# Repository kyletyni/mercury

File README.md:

This is a custom PCB and software design I created to compete in the APEC Micromouse 
competition in 2024. The design is based on the ESP32-S3 which is a dual core 
microprocessor. The pcb design was done in Kicad 7.0 and the MCU was programmed using 
the esp-idf utilizing RTOS for time dsensitive task scheduling.

Here is a link to an earlier hardware design running in a maze setting with 
control software:
<a href="https://www.youtube.com/watch?v=heloENtCQyA" target="_blank">Demo Video Link</a>

The PCB schematic consists of IR emitters and receivers, power modules, the MCU, 
gyro, encoders, and buttons.

This is what the PCB looked like when it was delivered.

Assembly complete! Software is still a work in progress, but all modules on the board
function individually as expected.

<div style="display:flex; justify-content:space-between;">

</div>

Layout of front and back layers of the board.
<div style="display:flex; justify-content:space-between;">

</div>

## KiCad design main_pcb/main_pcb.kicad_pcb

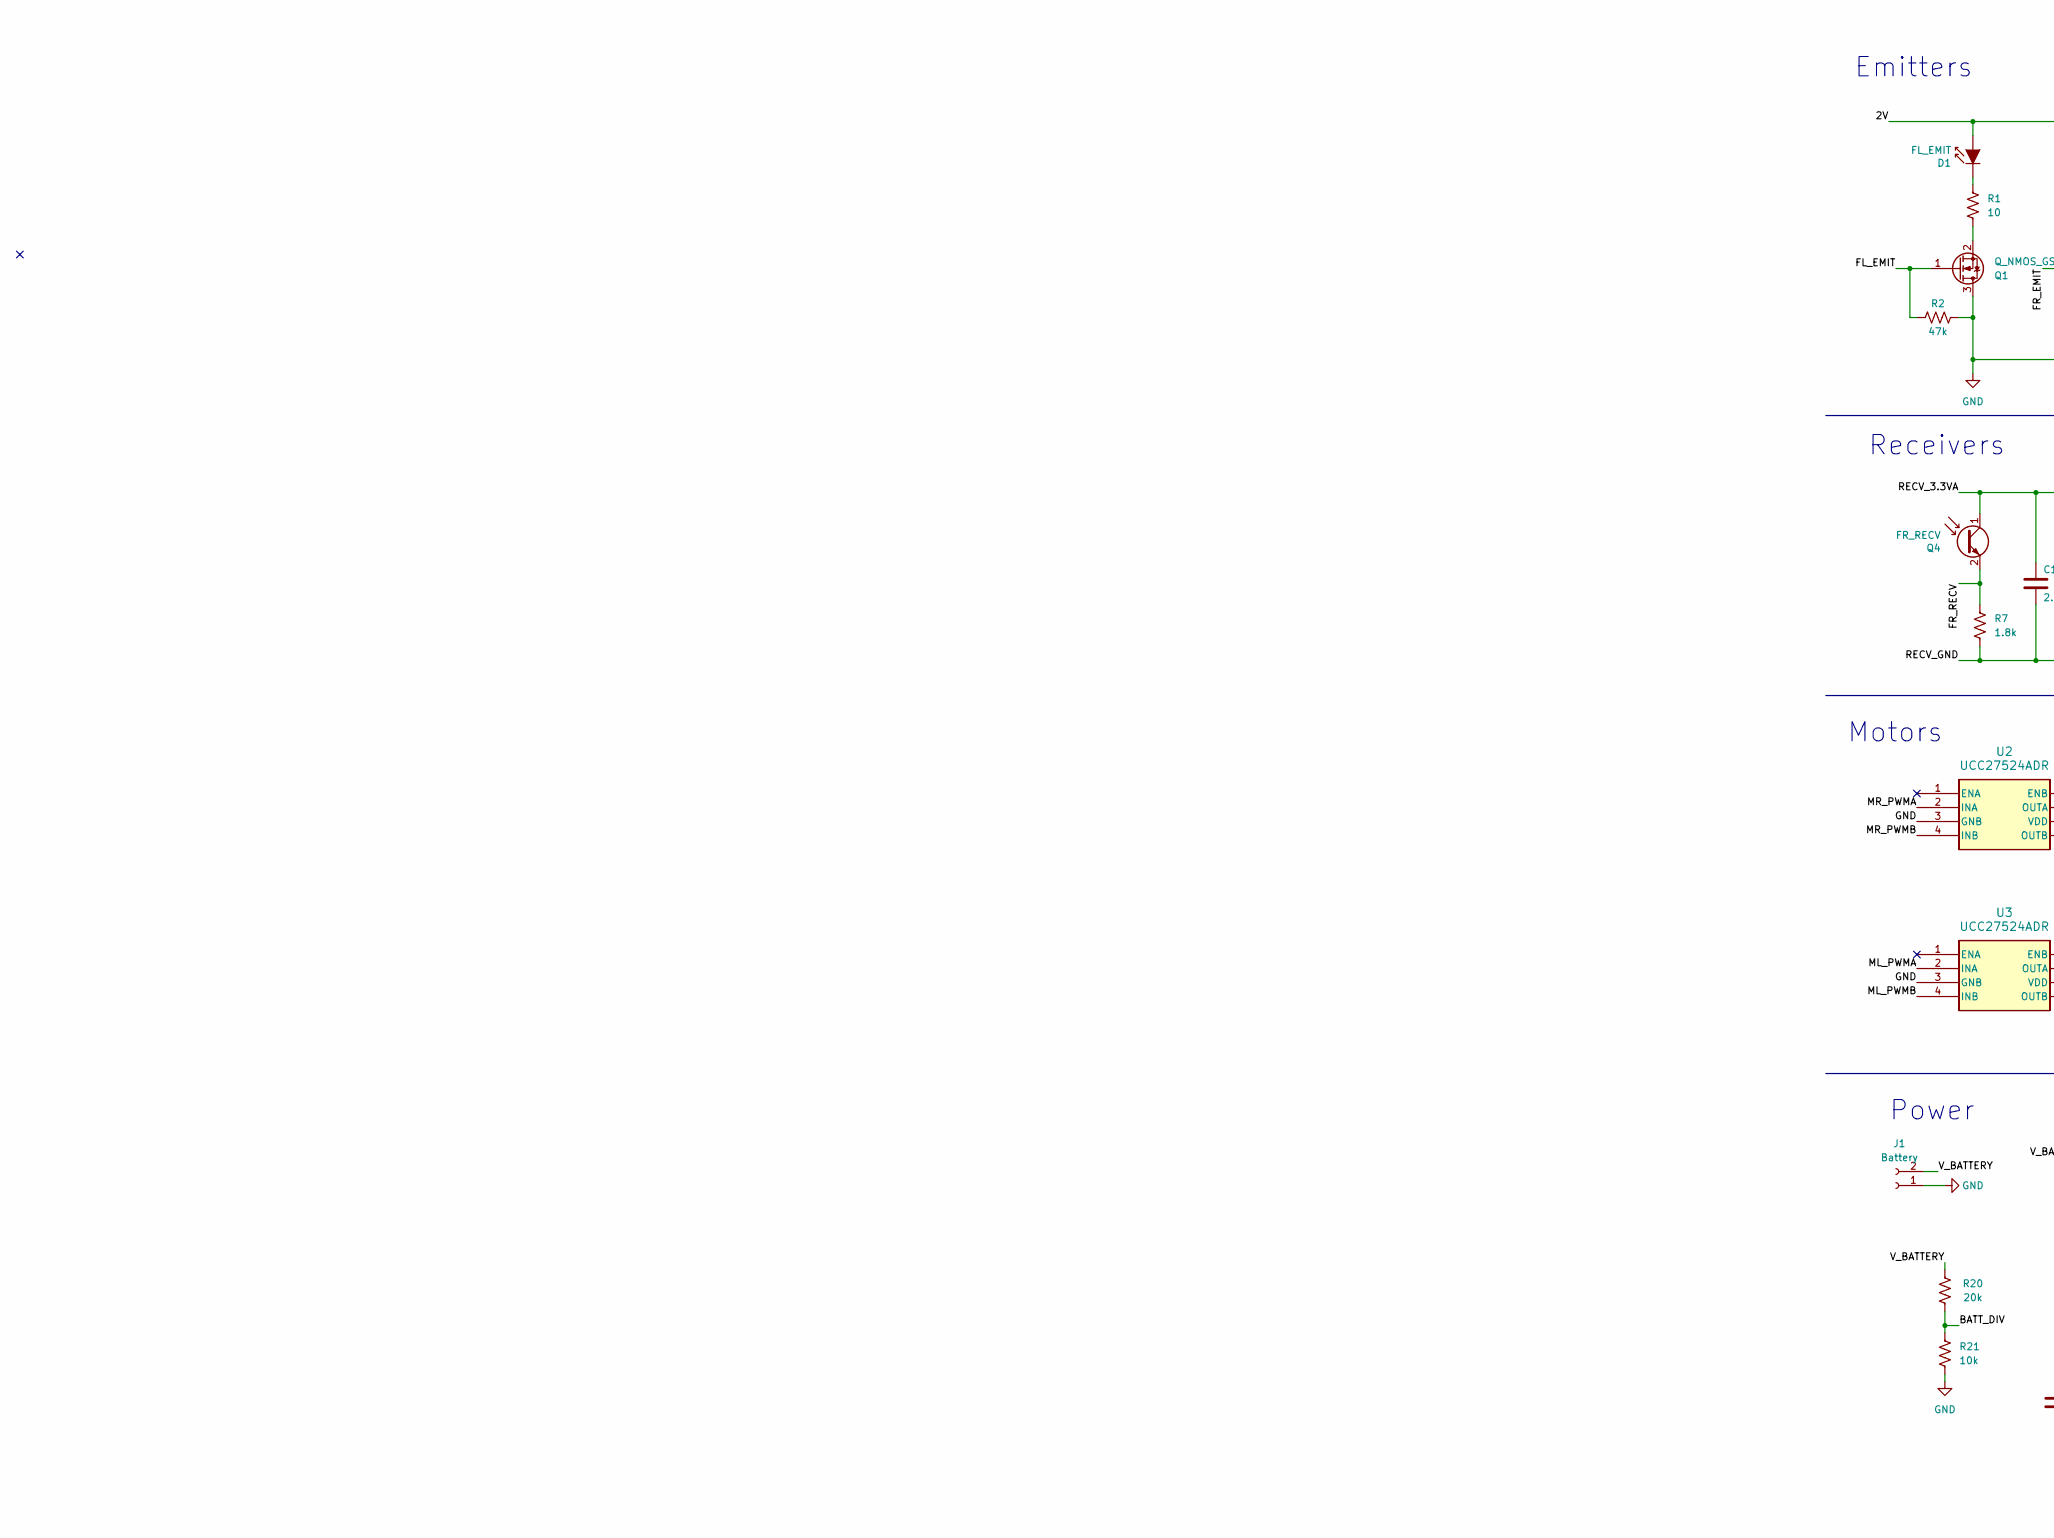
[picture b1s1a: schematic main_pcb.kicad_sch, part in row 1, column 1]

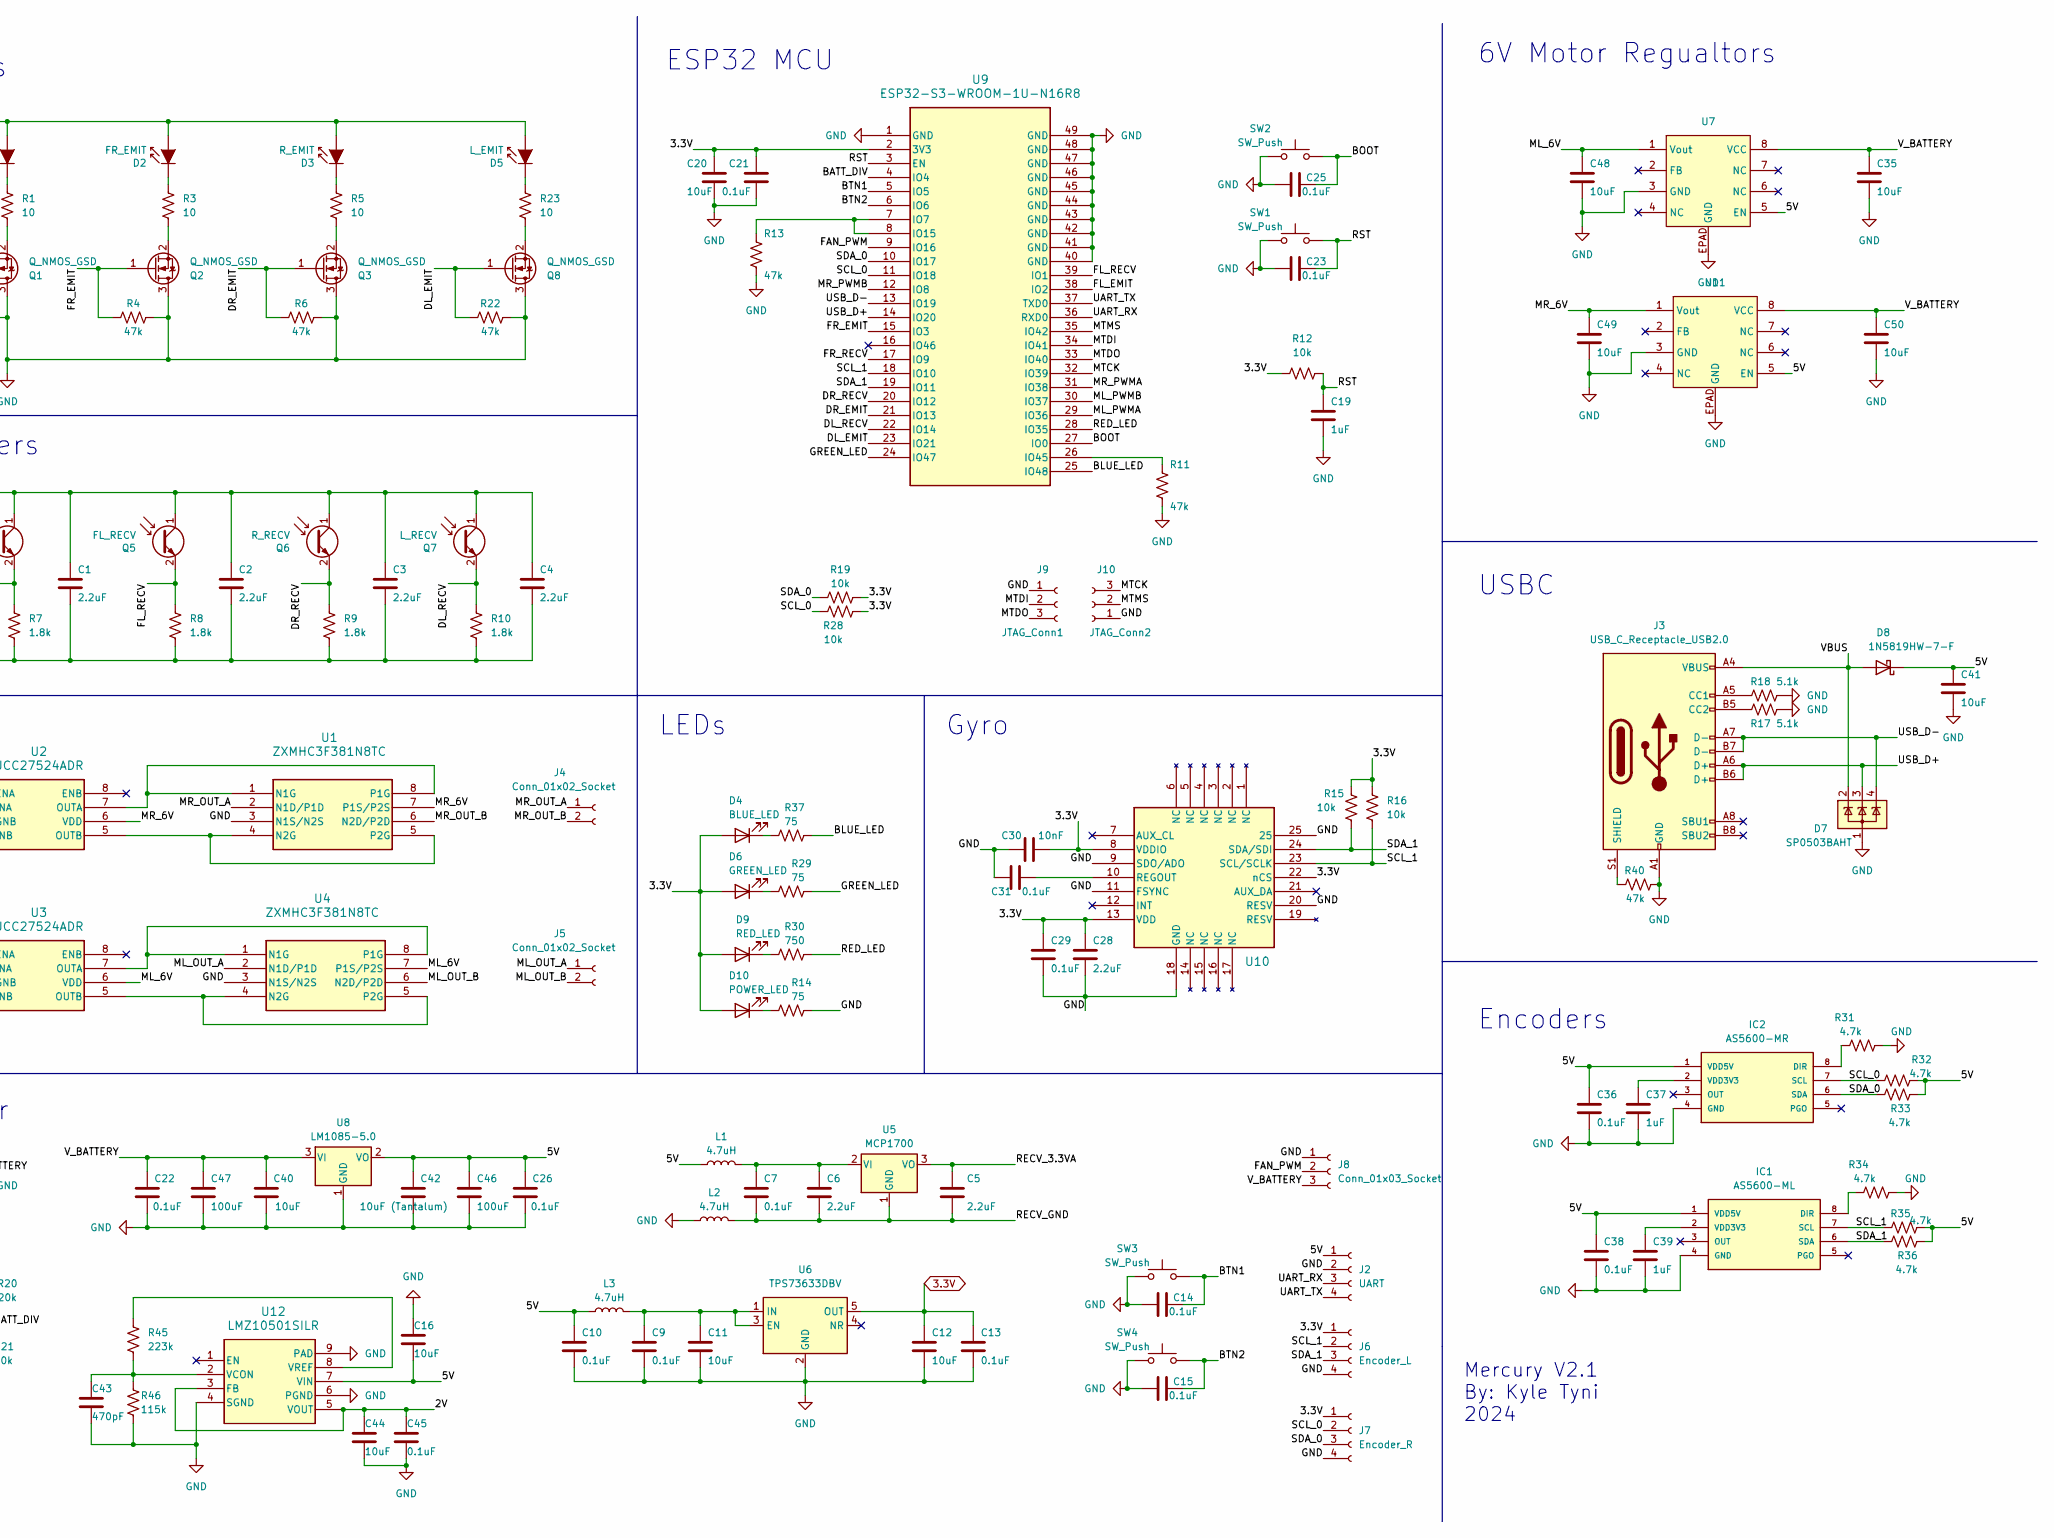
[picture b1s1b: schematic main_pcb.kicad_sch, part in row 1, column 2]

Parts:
C1, C2, C3, C4, C5, C6, C28: 2.2uF; C_0603_1608Metric_Pad1.08x0.95mm_HandSolder
C7, C9, C10, C13, C14, C15, C21, C22, C23, C25, C26, C29, C31, C36, C38, C45: 0.1uF; C_0603_1608Metric_Pad1.08x0.95mm_HandSolder
C11, C12, C16, C20, C35, C40, C41, C44, C48, C49, C50: 10uF; C_0603_1608Metric_Pad1.08x0.95mm_HandSolder
C19, C37, C39: 1uF; C_0603_1608Metric_Pad1.08x0.95mm_HandSolder
C30: 10nF; C_0603_1608Metric_Pad1.08x0.95mm_HandSolder
C42: 10uF (Tantalum); C_0603_1608Metric_Pad1.08x0.95mm_HandSolder
C43: 470pF; C_0603_1608Metric_Pad1.08x0.95mm_HandSolder
C46, C47: 100uF; CP_Radial_D5.0mm_P2.50mm
D1: FL_EMIT; Emitter
D2: FR_EMIT; Emitter
D3: R_EMIT; Emitter
D4: BLUE_LED; LED_0805_2012Metric_Pad1.15x1.40mm_HandSolder
D5: L_EMIT; Emitter
D6: GREEN_LED; LED_0805_2012Metric_Pad1.15x1.40mm_HandSolder
D7: SP0503BAHT; SOT-143
D8: 1N5819HW-7-F; 1N5819HW-7-F_DIO
D9: RED_LED; LED_0805_2012Metric_Pad1.15x1.40mm_HandSolder
D10: POWER_LED; LED_0805_2012Metric_Pad1.15x1.40mm_HandSolder
IC1: AS5600-ML; SOIC127P600X175-8N; MOUSER_PART_NUMBER 985-AS5600-ASOT
IC2: AS5600-MR; SOIC127P600X175-8N; MOUSER_PART_NUMBER 985-AS5600-ASOT
J1: Battery; PinSocket_1x02_P2.54mm_Vertical
J2: UART; PinHeader_1x04_P2.54mm_Vertical
J3: USB_C_Receptacle_USB2.0; USB_C_Receptacle_GCT_USB4085
J4, J5: Conn_01x02_Socket; PinSocket_1x02_P2.54mm_Vertical
J6: Encoder_L; PinHeader_1x04_P2.54mm_Vertical
J7: Encoder_R; PinHeader_1x04_P2.54mm_Vertical
J8: Conn_01x03_Socket; PinHeader_1x03_P2.54mm_Vertical
J9: JTAG_Conn1; PinHeader_1x03_P2.54mm_Vertical
J10: JTAG_Conn2; PinHeader_1x03_P2.54mm_Vertical
L1, L2, L3: 4.7uH; L_0603_1608Metric_Pad1.05x0.95mm_HandSolder
Q1, Q2, Q3, Q8: Q_NMOS_GSD; SOT-23
Q4: FR_RECV; IR_Reciever
Q5: FL_RECV; IR_Receiver_Mirrored
Q6: R_RECV; IR_Receiver_Mirrored
Q7: L_RECV; IR_Reciever
R1, R3, R5, R23: 10; R_0603_1608Metric_Pad0.98x0.95mm_HandSolder
R2, R4, R6, R11, R13, R22, R40: 47k; R_0603_1608Metric_Pad0.98x0.95mm_HandSolder
R7, R8, R9, R10: 1.8k; R_0603_1608Metric_Pad0.98x0.95mm_HandSolder
R12, R15, R16, R19, R21, R28: 10k; R_0603_1608Metric_Pad0.98x0.95mm_HandSolder
R14, R29, R37: 75; R_0603_1608Metric_Pad0.98x0.95mm_HandSolder
R17, R18: 5.1k; R_0603_1608Metric_Pad0.98x0.95mm_HandSolder
R20: 20k; R_0603_1608Metric_Pad0.98x0.95mm_HandSolder
R30: 750; R_0603_1608Metric_Pad0.98x0.95mm_HandSolder
R31, R32, R33, R34, R35, R36: 4.7k; R_0603_1608Metric_Pad0.98x0.95mm_HandSolder
R45: 223k; R_0603_1608Metric_Pad0.98x0.95mm_HandSolder
R46: 115k; R_0603_1608Metric_Pad0.98x0.95mm_HandSolder
SW1, SW2, SW3, SW4: SW_Push; SW_SPST_REED_CT05-XXXX-G1
U1, U4: ZXMHC3F381N8TC; SOIC_81N8TC_DIO
U2, U3: UCC27524ADR; D8_TEX
U5: MCP1700; SOT-89-3
U6: TPS73633DBV; SOT-23-5
U7, U11: HTSOP-J8_ROM
U8: LM1085-5.0; 5V Voltage Reg
U9: ESP32-S3-WROOM-1U-N16R8; ESP32­S3­WROOM­1U_EXP
U10: MPU-6500; QFN24_3X3X0P9_IVS
U12: LMZ10501SILR; SIL0008A

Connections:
3.3V: C12.1, C13.1, C20.1, C21.1, C28.1, C29.1, C30.2, D4.2 (A), D6.2 (A), D9.2 (A), D10.2 (A), J6.1, J7.1, R12.1, R15.1, R16.1, R19.2, R28.2, U6.5 (OUT), U9.2 (3V3), U10.8 (VDDIO), U10.13 (VDD), U10.22 (nCS)
/2V: C44.1, C45.1, D1.2 (A), D2.2 (A), D3.2 (A), D5.2 (A), U12.3 (FB), U12.5 (VOUT)
/5V: C10.1, C16.2, C26.2, C36.1, C38.1, C41.1, C42.2, C46.1, D8.1 (K), IC1.1 (VDD5V), IC2.1 (VDD5V), J2.1, L1.1, L3.1, R32.2, R33.2, R35.2, R36.2, U7.5 (EN), U8.2 (VO), U11.5 (EN), U12.7 (VIN)
/BATT_DIV: R20.1, R21.1, U9.4 (IO4)
/BLUE_LED: R37.2, U9.25 (IO48)
/BOOT: C25.1, SW2.2, U9.27 (IO0)
/BTN1: C14.1, SW3.2, U9.5 (IO5)
/BTN2: C15.1, SW4.2, U9.6 (IO6)
/DL_EMIT: Q8.1 (G), R22.1, U9.23 (IO21)
/DL_RECV: Q7.2 (E), R10.1, U9.22 (IO14)
/DR_EMIT: Q3.1 (G), R6.1, U9.21 (IO13)
/DR_RECV: Q6.2 (E), R9.1, U9.20 (IO12)
/FAN_PWM: J8.2, U9.9 (IO16)
/FL_EMIT: Q1.1 (G), R2.1, U9.38 (IO2)
/FL_RECV: Q5.2 (E), R8.1, U9.39 (IO1)
/FR_EMIT: Q2.1 (G), R4.1, U9.15 (IO3)
/FR_RECV: Q4.2 (E), R7.1, U9.17 (IO9)
/GREEN_LED: R29.2, U9.24 (IO47)
/ML_6V: C48.1, U3.6 (VDD), U4.7 (P1S/P2S), U7.1 (Vout)
/ML_OUT_A: J5.1, U4.2 (N1D/P1D)
/ML_OUT_B: J5.2, U4.6 (N2D/P2D)
/ML_PWMA: U3.2 (INA), U9.29 (IO36)
/ML_PWMB: U3.4 (INB), U9.30 (IO37)
/MR_6V: C49.1, U1.7 (P1S/P2S), U2.6 (VDD), U11.1 (Vout)
/MR_OUT_A: J4.1, U1.2 (N1D/P1D)
/MR_OUT_B: J4.2, U1.6 (N2D/P2D)
/MR_PWMA: U2.2 (INA), U9.31 (IO38)
/MR_PWMB: U2.4 (INB), U9.12 (IO8)
/MTCK: J10.3, U9.32 (IO39)
/MTDI: J9.2, U9.34 (IO41)
/MTDO: J9.3, U9.33 (IO40)
/MTMS: J10.2, U9.35 (IO42)
/RECV_3.3VA: C1.1, C2.1, C3.1, C4.1, C5.1, Q4.1 (C), Q5.1 (C), Q6.1 (C), Q7.1 (C), U5.3 (VO)
/RECV_GND: C1.2, C2.2, C3.2, C4.2, C5.2, C6.2, C7.2, L2.2, R7.2, R8.2, R9.2, R10.2, U5.1 (GND)
/RED_LED: R30.2, U9.28 (IO35)
/RST: C19.1, C23.1, R12.2, SW1.2, U9.3 (EN)
/SCL_0: IC2.7 (SCL), J7.2, R28.1, R32.1, U9.11 (IO18)
/SCL_1: IC1.7 (SCL), J6.2, R16.2, R35.1, U9.18 (IO10), U10.23 (SCL/SCLK)
/SDA_0: IC2.6 (SDA), J7.3, R19.1, R33.1, U9.10 (IO17)
/SDA_1: IC1.6 (SDA), J6.3, R15.2, R36.1, U9.19 (IO11), U10.24 (SDA/SDI)
/UART_RX: J2.3, U9.36 (RXD0)
/UART_TX: J2.4, U9.37 (TXD0)
/USB_D+: D7.3 (K), J3.A6 (D+), J3.B6 (D+), U9.14 (IO20)
/USB_D-: D7.4 (K), J3.A7 (D-), J3.B7 (D-), U9.13 (IO19)
/VBUS: D7.2 (K), D8.2 (A), J3.A4 (VBUS), J3.A9 (VBUS), J3.B4 (VBUS), J3.B9 (VBUS)
/V_BATTERY: C22.2, C35.1, C40.2, C47.1, C50.1, J1.2, J8.3, R20.2, U7.8 (VCC), U8.3 (VI), U11.8 (VCC)
GND: C9.2, C10.2, C11.2, C12.2, C13.2, C14.2, C15.2, C16.1, C19.2, C20.2, C21.2, C22.1, C23.2, C25.2, C26.1, C28.2, C29.2, C30.1, C31.1, C35.2, C36.2, C37.2, C38.2, C39.2, C40.1, C41.2, C42.1, C43.2, C44.2, C45.2, C46.2, C47.2, C48.2, C49.2, C50.2, D7.1 (A), IC1.4 (GND), IC2.4 (GND), J1.1, J2.2, J3.A1 (GND), J3.A12 (GND), J3.B1 (GND), J3.B12 (GND), J6.4, J7.4, J8.1, J9.1, J10.1, L2.1, Q1.3 (D), Q2.3 (D), Q3.3 (D), Q8.3 (D), R2.2, R4.2, R6.2, R11.1, R13.1, R14.2, R17.2, R18.2, R21.2, R22.2, R31.2, R34.2, R40.2, R46.2, SW1.1, SW2.1, SW3.1, SW4.1, U1.3 (N1S/N2S), U2.3 (GNB), U3.3 (GNB), U4.3 (N1S/N2S), U6.2 (GND), U7.3 (GND), U7.EPAD (GND), U8.1 (GND), U9.1 (GND), U9.40 (GND), U9.41 (GND), U9.42 (GND), U9.43 (GND), U9.44 (GND), U9.45 (GND), U9.46 (GND), U9.47 (GND), U9.48 (GND), U9.49 (GND), U10.9 (SDO/ADO), U10.11 (FSYNC), U10.18 (GND), U10.20 (RESV), U10.25, U11.3 (GND), U11.EPAD (GND), U12.4 (SGND), U12.6 (PGND), U12.9 (PAD)
unnamed: C37.1, IC2.2 (VDD3V3)
unnamed: C39.1, IC1.2 (VDD3V3)
unnamed: D1.1 (K), R1.1
unnamed: D2.1 (K), R3.1
unnamed: D3.1 (K), R5.1
unnamed: D4.1 (K), R37.1
unnamed: D5.1 (K), R23.1
unnamed: D6.1 (K), R29.1
unnamed: D9.1 (K), R30.1
unnamed: D10.1 (K), R14.1
unnamed: IC1.8 (DIR), R34.1
unnamed: IC2.8 (DIR), R31.1
unnamed: J3.A5 (CC1), R18.1
unnamed: J3.B5 (CC2), R17.1
unnamed: J3.S1 (SHIELD), R40.1
unnamed: Q1.2 (S), R1.2
unnamed: Q2.2 (S), R3.2
unnamed: Q3.2 (S), R5.2
unnamed: Q8.2 (S), R23.2
unnamed: U1.1 (N1G), U1.8 (P1G), U2.7 (OUTA)
unnamed: U1.4 (N2G), U1.5 (P2G), U2.5 (OUTB)
unnamed: U3.7 (OUTA), U4.1 (N1G), U4.8 (P1G)
unnamed: U3.5 (OUTB), U4.4 (N2G), U4.5 (P2G)
unnamed: C6.1, C7.1, L1.2, U5.2 (VI)
unnamed: C9.1, C11.1, L3.2, U6.1 (IN), U6.3 (EN)
unnamed: R13.2, U9.7 (IO7), U9.8 (IO15)
unnamed: R11.2, U9.26 (IO45)
unnamed: C31.2, U10.10 (REGOUT)
unnamed: C43.1, R45.2, R46.1, U12.2 (VCON)
unnamed: R45.1, U12.8 (VREF)

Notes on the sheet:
USBC
LEDs
Power
6V Motor Regualtors
Encoders
Emitters
Motors
Mercury V2.1 By: Kyle Tyni 2024
Gyro
ESP32 MCU
Receivers

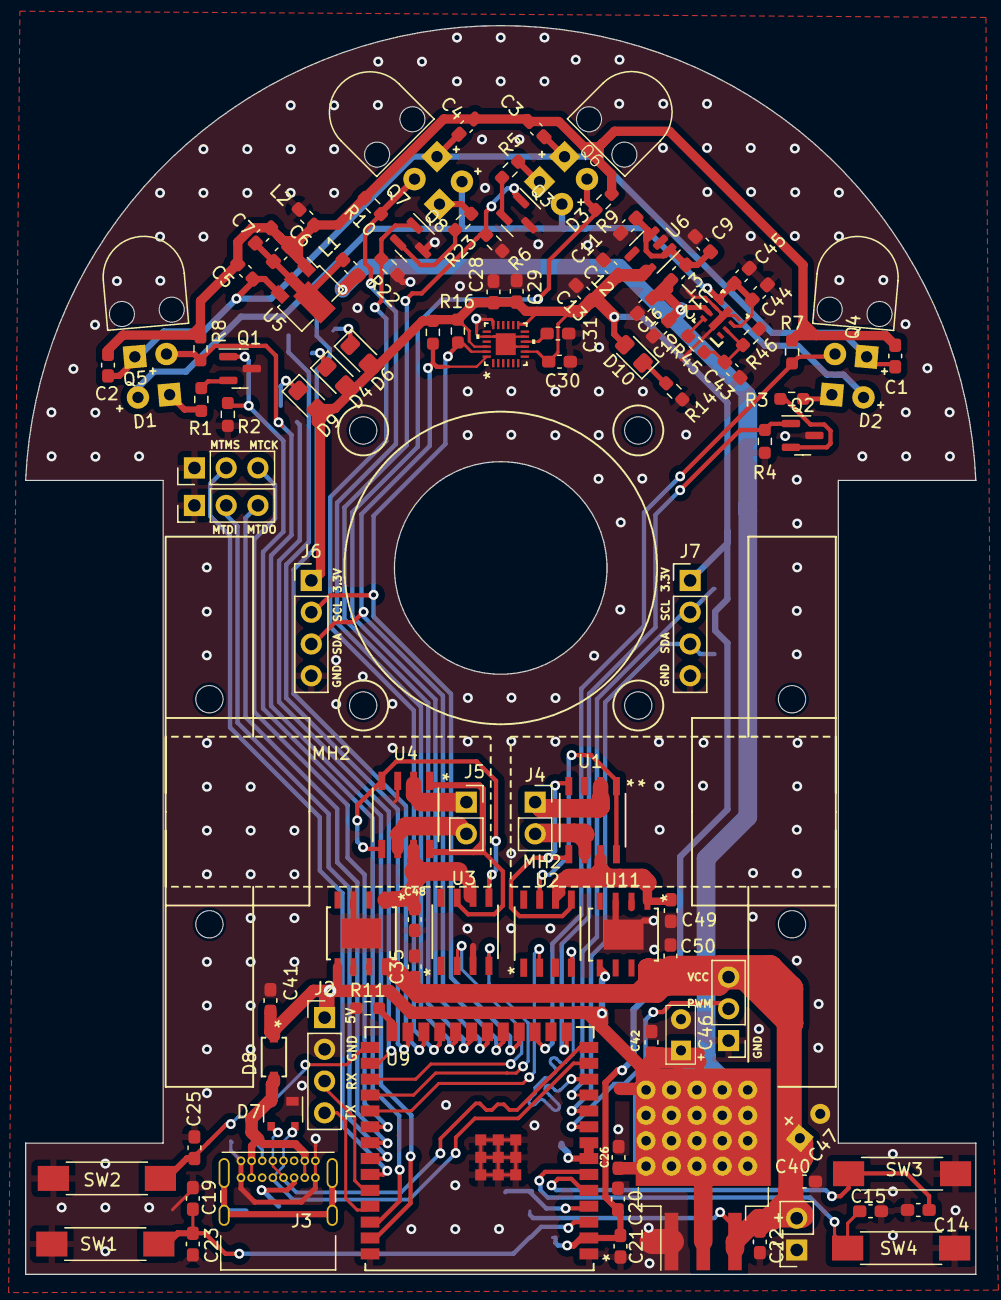
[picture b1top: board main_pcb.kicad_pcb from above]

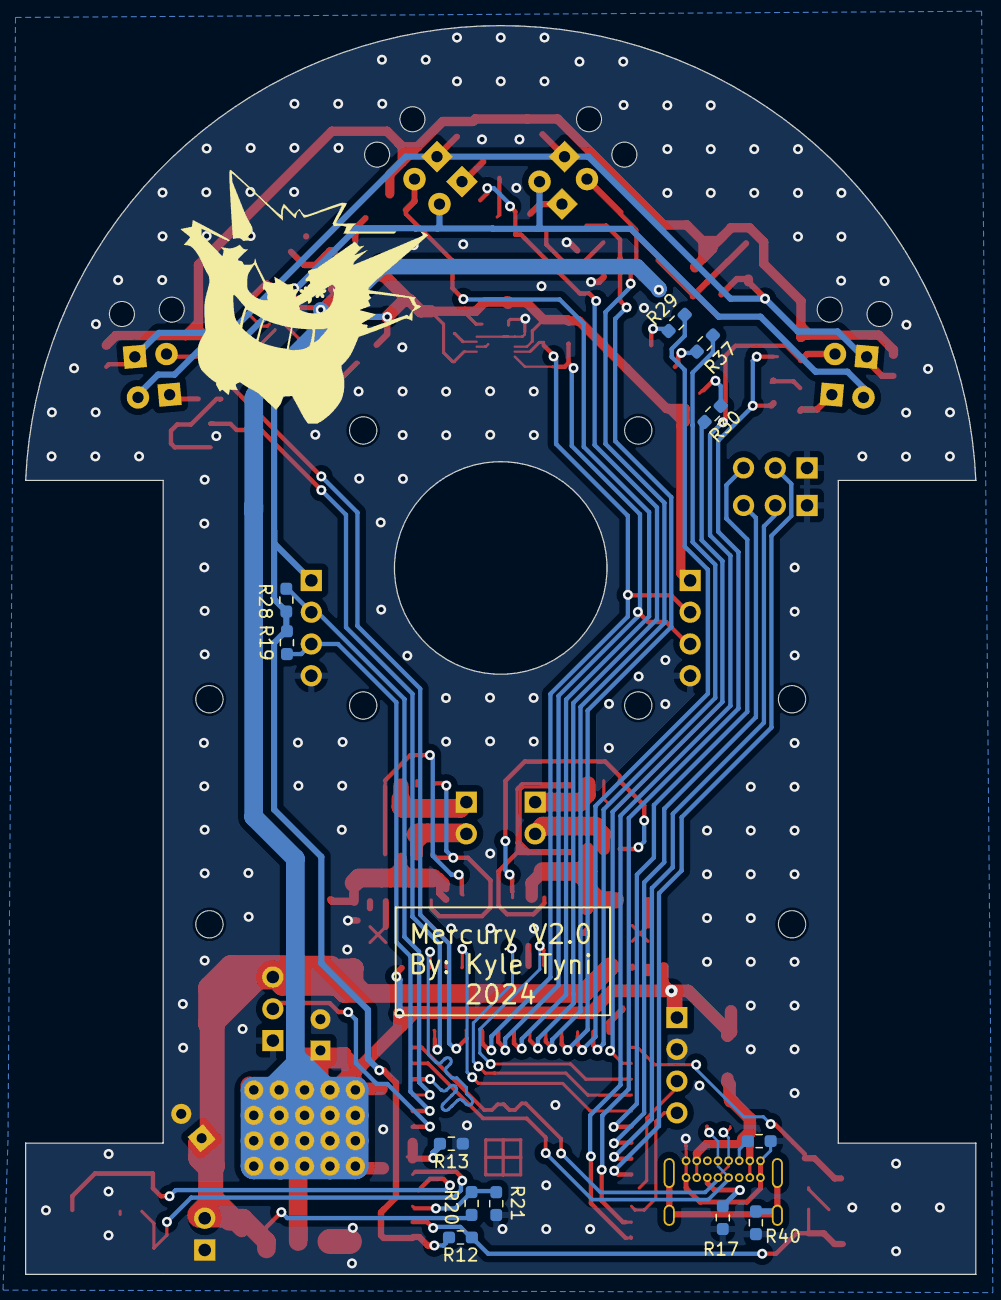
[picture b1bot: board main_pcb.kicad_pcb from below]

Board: 2 copper layers, 76.0 x 99.9 mm, 117 parts (12 on the bottom side), 73 nets.

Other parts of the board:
MH2, MH2#2: M2_MH; Motor

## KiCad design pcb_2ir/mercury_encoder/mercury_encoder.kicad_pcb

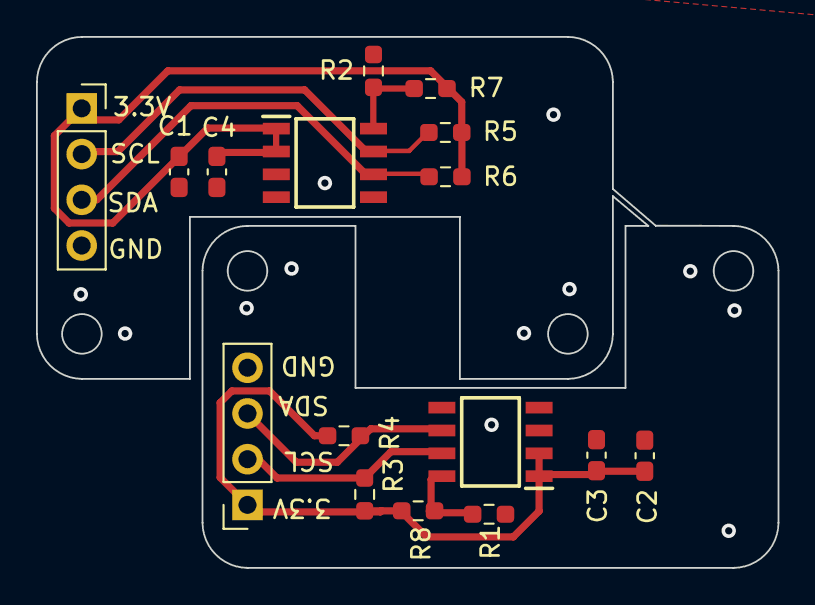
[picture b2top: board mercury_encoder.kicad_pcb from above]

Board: 2 copper layers, 41.2 x 29.5 mm, 16 parts (0 on the bottom side), 8 nets.

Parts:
C1, C2: 0.1uF; C_0603_1608Metric_Pad1.08x0.95mm_HandSolder
C3, C4: 1uF; C_0603_1608Metric_Pad1.08x0.95mm_HandSolder
IC1: AS5600-MR; SOIC127P600X175-8N
IC2: AS5600-ML; SOIC127P600X175-8N
J1: ML_Conn; PinSocket_1x04_P2.54mm_Vertical
J2: MR_Conn; PinSocket_1x04_P2.54mm_Vertical
R1, R2, R3, R4, R5, R6, R7, R8: 4.7k; R_0603_1608Metric_Pad0.98x0.95mm_HandSolder

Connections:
/3.3V: C1.1, C2.1, C3.1, C4.1, IC1.1 (VDD5V), IC1.2 (VDD3V3), IC2.1 (VDD5V), IC2.2 (VDD3V3), J1.1, J2.1, R3.2, R4.2, R5.2, R6.2, R7.2, R8.2
/SCL_0: IC1.7 (SCL), J1.2, R3.1
/SCL_1: IC2.7 (SCL), J2.2, R5.1
/SDA_0: IC1.6 (SDA), J1.3, R4.1
/SDA_1: IC2.6 (SDA), J2.3, R6.1
GND: C1.2, C2.2, C3.2, C4.2, IC1.4 (GND), IC2.4 (GND), J1.4, J2.4, R1.2, R2.2
unnamed: IC1.8 (DIR), R1.1, R8.1
unnamed: IC2.8 (DIR), R2.1, R7.1

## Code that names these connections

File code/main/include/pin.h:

#ifndef PIN_H
#define PIN_H

#include <stdio.h>
#include "freertos/FreeRTOS.h"
#include "freertos/task.h"
#include "driver/gpio.h"

/******************* Emitter + Receiver Pins *******************/
// Front Left IR Pins
#define FL_RECV_PIN GPIO_NUM_1
#define FL_EMIT_PIN GPIO_NUM_2

// Front Right IR Pins
#define FR_RECV_PIN GPIO_NUM_9
#define FR_EMIT_PIN GPIO_NUM_3

// Diagonal Right IR Pins
#define DL_RECV_PIN GPIO_NUM_14
#define DL_EMIT_PIN GPIO_NUM_21

// Diagonal Left IR Pins
#define DR_RECV_PIN GPIO_NUM_12
#define DR_EMIT_PIN GPIO_NUM_13

/******************* Motor PWM Pins *******************/
// Right Motor
#define MR_PWMA_PIN GPIO_NUM_38
#define MR_PWMB_PIN GPIO_NUM_8

// Left Motor
#define ML_PWMA_PIN GPIO_NUM_36
#define ML_PWMB_PIN GPIO_NUM_37

// Fan Motor
#define FAN_PWM_PIN GPIO_NUM_16

/******************* Button Pins *******************/
#define BTN1 GPIO_NUM_5
#define BTN2 GPIO_NUM_6

/******************* LED Pins *******************/
#define RED_LED GPIO_NUM_35
#define BLUE_LED GPIO_NUM_48
#define GREEN_LED GPIO_NUM_47


void initialize_emitter_output_pin(gpio_num_t gpio_num) {
    gpio_config_t io_conf = {
        .pin_bit_mask = (1ULL << gpio_num),
        .mode = GPIO_MODE_OUTPUT,
        .pull_up_en = GPIO_PULLUP_DISABLE,
        .pull_down_en = GPIO_PULLDOWN_DISABLE,
        .intr_type = GPIO_INTR_DISABLE
    };
    ESP_ERROR_CHECK(gpio_config(&io_conf));
}

#endif

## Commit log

2023-12-10 intial commit, added starting pcb files and esp32 code
2023-12-12 added more to pcb, esp32, gyro, usbc
2024-01-02 first completerouting of PCB
2024-01-25 completed 4 sensor pcb
2024-01-30 pcb fixes and unit test code for each module of pcb
2024-01-31 cleaned file structure
2024-01-31 added pcb schematic image
2024-01-31 Update README.md with schematic image
2024-01-31 added more images to readme
2024-01-31 more readme updates
2024-01-31 updated readme with correct links to images
2024-01-31 updated image widths in readme
2024-01-31 resized images
2024-01-31 resized and put images on the same row
2024-01-31 more updates to image sizing
2024-01-31 updated sizes again
2024-01-31 changed image extension to png
2024-01-31 added youtube link to readme
2024-01-31 updated youtube link
2024-01-31 added link for youtube video to readme
2024-02-12 added basic motor control profiles
2024-02-15 added IR tuning and floodfill capability
2024-02-24 added basic search implementation
2024-03-01 changes to sensor tuning values for APEC
